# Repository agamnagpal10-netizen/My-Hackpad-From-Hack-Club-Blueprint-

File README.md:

# My-Hackpad-From-Hack-Club-Blueprint-

**Built for Hack Club** 

This is my first ever build from scratch. This is a macropad with 6 keys, made by using the tutorial provided by Hack Club.

My name is **Agam**, and I am a sophomore student. I want to be some kind of engineer, so when I saw this project I thought I would a shot at it to learn how a PCB works, schematic, and the softwares. 

I mainly used **KiCad** for the schematic and the main PCB wiring. Then I moved onto **Fusion 360**, working on the bottom and top case to house the microcontroller and everything else. 

## What Everything Is

### 1. Schematic

This was the first step in making my macropad. You can find the screenshots of the Schematic in the folder named "Screenshots". Below, I have the images just incase you want to see them!

### 2. PCB

The was the second step in making my macropad. As with the schematic, you can find the image in the folder named "Screenshots". Image is also below!

### 3. Case_Files
These are 3D files that are printable that hold the PCB and keys, which makes everything work together in the macropad

### 4. Keyboard_Keycaps
This is the file which are the dimensions of the actual Cherry MX Keycaps, so the case fits on top of the keys.

### 5. Case Screenshots (Fusion 360)

### 6. main.py
This is the code file for the keyboard, which allows the keyboard to be properly coded and work with my laptop. I just used the code from Blueprint, however I am still trying to learn how to code this properly so I can make future projects.

# BOM
1 Seeed XIAO RP2040

6 Cherry MX-style switches

6 Keycaps

4 Screws

4 Heatset inserts

1 3D printed case (find the CAD files in /case)

Thank you for checking out my macropad project!

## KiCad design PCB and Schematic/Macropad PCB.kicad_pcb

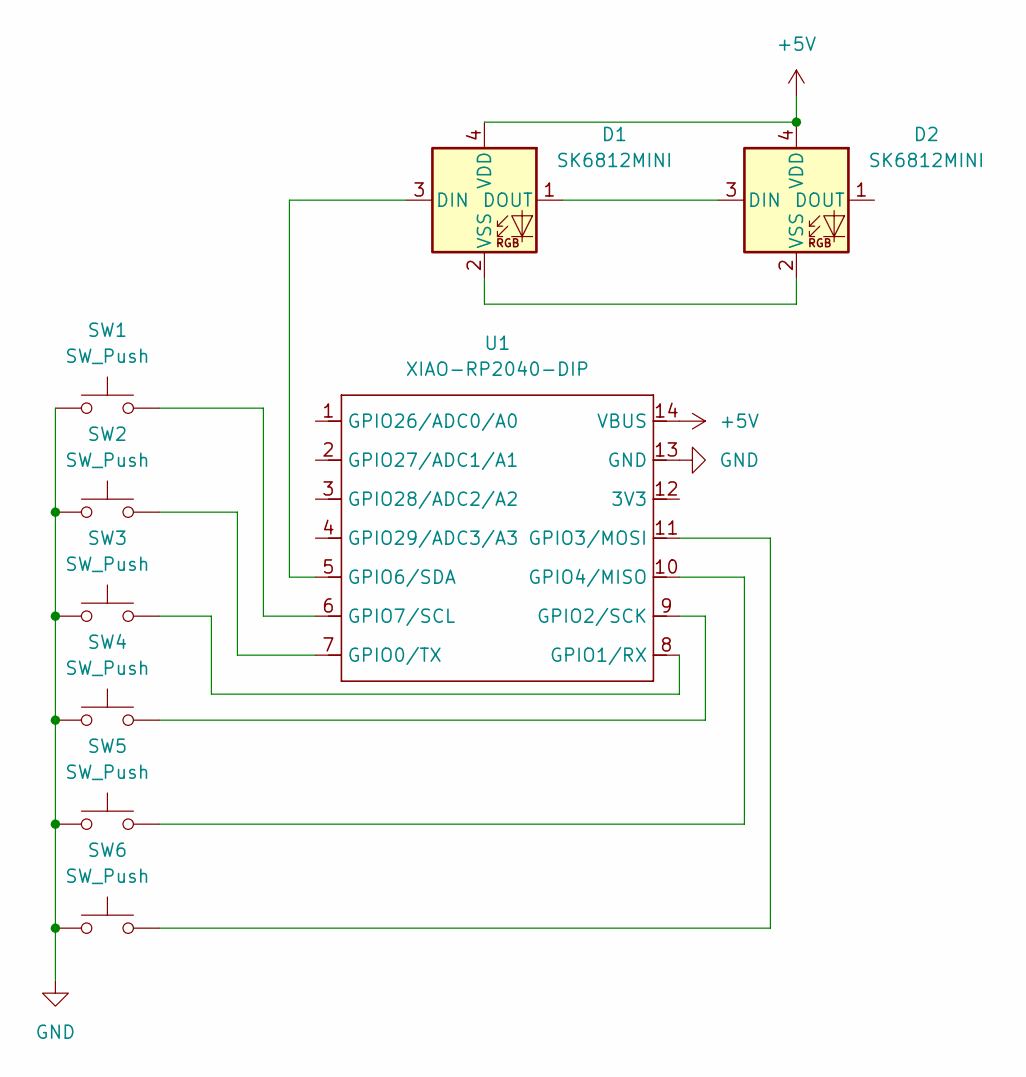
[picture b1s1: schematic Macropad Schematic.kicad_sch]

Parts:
D1, D2: SK6812MINI; LED_SK6812MINI_PLCC4_3.5x3.5mm_P1.75mm
SW1, SW2, SW3, SW4, SW5, SW6: SW_Push; SW_Cherry_MX_1.00u_PCB
U1: XIAO-RP2040-DIP

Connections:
+5V: D1.4 (VDD), D2.4 (VDD), U1.14 (VBUS)
GND: SW1.1, SW2.1, SW3.1, SW4.1, SW5.1, SW6.1, U1.13 (GND)
unnamed: D1.3 (DIN), U1.5 (GPIO6/SDA)
unnamed: D1.1 (DOUT), D2.3 (DIN)
unnamed: D1.2 (VSS), D2.2 (VSS)
unnamed: SW2.2, U1.7 (GPIO0/TX)
unnamed: SW3.2, U1.8 (GPIO1/RX)
unnamed: SW4.2, U1.9 (GPIO2/SCK)
unnamed: SW6.2, U1.11 (GPIO3/MOSI)
unnamed: SW5.2, U1.10 (GPIO4/MISO)
unnamed: SW1.2, U1.6 (GPIO7/SCL)

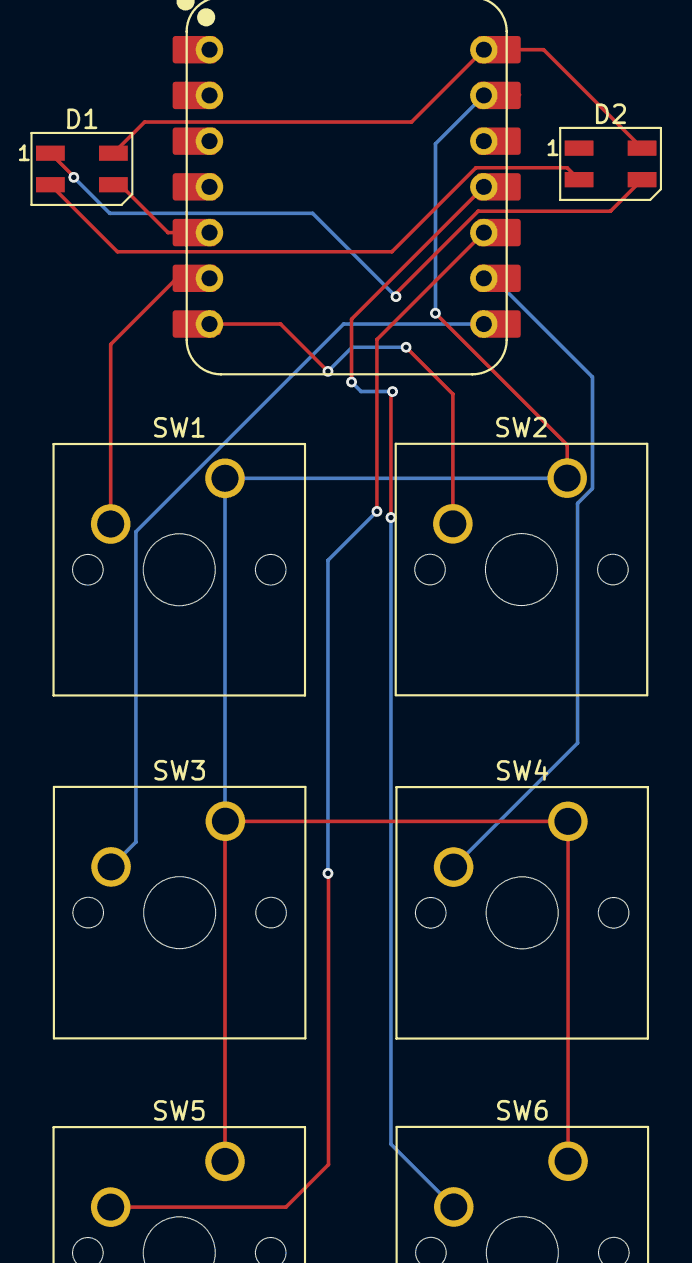
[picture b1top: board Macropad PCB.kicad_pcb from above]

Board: 2 copper layers, 9 parts (0 on the bottom side), 11 nets.

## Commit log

2026-02-24 README.md
2026-02-24 Create temp
2026-02-24 Create Wiring
2026-02-24 Create PCB
2026-02-24 PCB and Schematic/PCB
2026-02-24 Create Keys
2026-02-24 Keys-Layout/Keys
2026-02-24 Create Code
2026-02-24 Firmware/Code
